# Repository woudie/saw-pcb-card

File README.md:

# Saw PCB Card

This is a fun little project for a pcb buisiness card inspired by a similar project that I saw online.

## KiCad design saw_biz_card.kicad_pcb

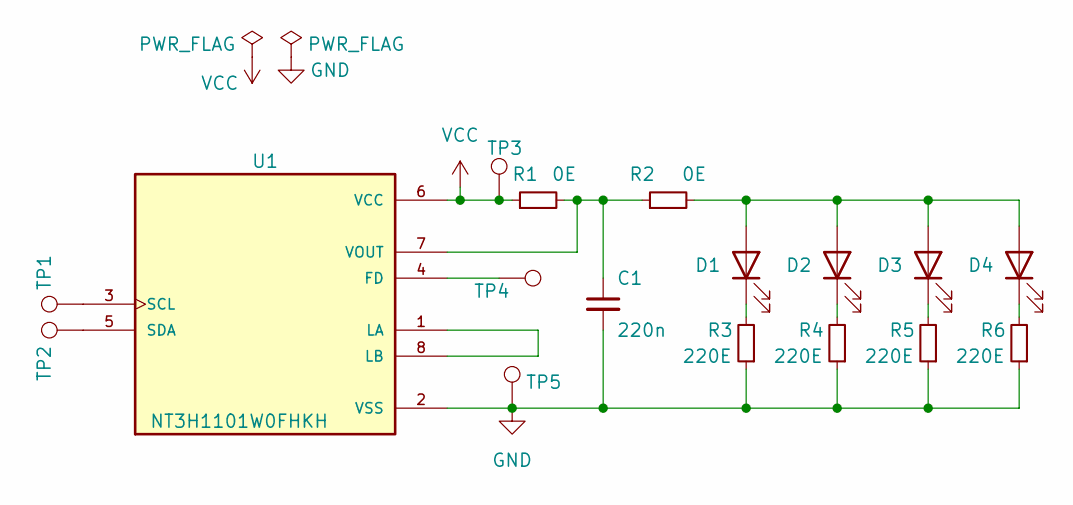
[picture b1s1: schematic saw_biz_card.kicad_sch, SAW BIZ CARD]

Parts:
C1: 220n; C_0402_1005Metric
D1, D2, D3, D4: LED; LED_0402_1005Metric
R1, R2: 0E; R_0402_1005Metric
R3, R4, R5, R6: 220E; R_0402_1005Metric
TP1, TP2, TP3, TP4, TP5: TestPoint; TestPoint_Pad_D1.0mm
U1: NT3H1101W0FHKH; IC_NT3H1101W0FHKH; PARTREV 3.3

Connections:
GND: C1.2, R3.1, R4.1, R5.1, R6.1, TP5.1, U1.2 (VSS)
unnamed: C1.1, R1.2, R2.1, U1.7 (VOUT)
unnamed: D1.1 (K), R3.2
unnamed: D1.2 (A), D2.2 (A), D3.2 (A), D4.2 (A), R2.2
unnamed: D2.1 (K), R4.2
unnamed: D3.1 (K), R5.2
unnamed: D4.1 (K), R6.2
unnamed: TP1.1, U1.3 (SCL)
unnamed: TP2.1, U1.5 (SDA)
unnamed: TP4.1, U1.4 (FD)
unnamed: U1.1 (LA), U1.8 (LB)
VCC: R1.1, TP3.1, U1.6 (VCC)

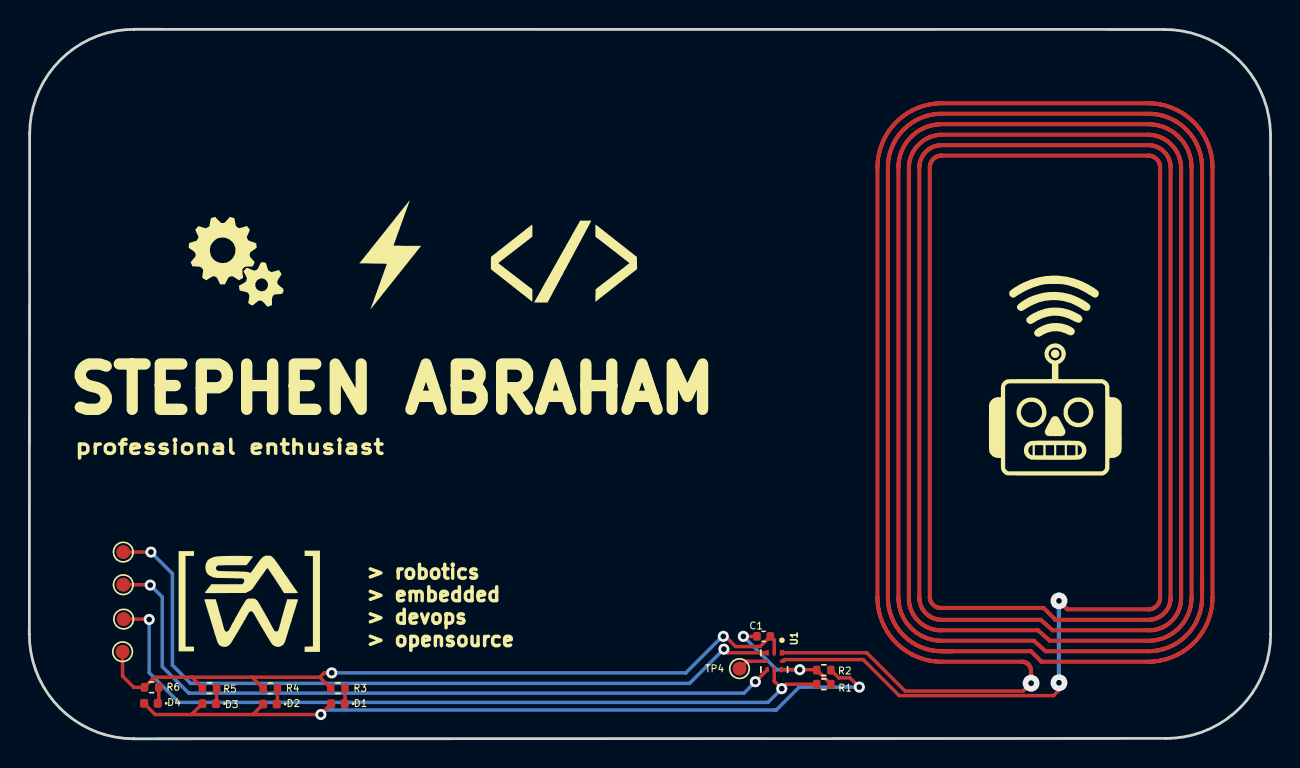
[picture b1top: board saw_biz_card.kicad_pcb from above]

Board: 2 copper layers, 88.9 x 50.8 mm, 17 parts (0 on the bottom side), 12 nets.

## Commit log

2023-01-30 initial commit.
    Added relevant custom symbols and footprints.
    completed basic schematic.
    completed basic layout.
2023-01-30 updated gitignore and README
2023-02-28 test
2023-02-28 temp
2023-02-28 testyboi
2023-02-28 Rename feature_request.md to feature_request.yaml
2023-02-28 Rename bug_pr.md to bug_pr.yaml
